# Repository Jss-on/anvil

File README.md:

# Anvil

**Hardware product development with explicit release gates and revision-bound evidence.**
Version **0.6.0** · Claude Code and Codex plugins · Proprietary license

Anvil carries a product from requirements and architecture through PCB fabrication, firmware,
mechanics, integration, EVT/DVT/PVT, market release, support and retirement. Its commands perform
authorized engineering work and keep missing external tests or approvals visible as blockers.

```mermaid
flowchart LR
  G0["G0 Opportunity"] --> G1["G1 Requirements"] --> G2["G2 Architecture"]
  G2 --> G3["G3 Prototype release"] --> G4["G4 EVT"] --> G5["G5 DVT"]
  G5 --> G6["G6 PVT"] --> G7["G7 Market release"] --> S["Support and retirement"]
  S -->|Controlled changes| G2
```

Electronics, firmware/services, mechanics, supply/manufacturing, quality/compliance and commercial
work proceed concurrently. The [lifecycle protocol](.claude/skills/anvil/references/lifecycle-protocol.md)
defines gates, owners, artifacts and checklists. The [research report](research/hardware-product-lifecycle.md)
and [original assessment](ASSESSMENT.md) explain the upgrade's basis.

## Use with Claude Code

Install the repository's marketplace in Claude Code, then its `anvil` plugin:

```text
/plugin marketplace add Jss-on/anvil
/plugin install anvil@anvil
```

For local development, load the actual packaged directory with `claude --plugin-dir ./claude-plugin`.
The repository's canonical command and skill files also support project-local development.
Do not assume editing this checkout changes an already cached installation; reload the local
plugin or update the installed package after publishing an authorized release.

| Command | Purpose |
|---|---|
| `/anvil` | Bounded custom metric loop or task routing |
| `/anvil:requirements` | Requirements, methods, owners, verification gates and applicability |
| `/anvil:build` | Concurrent product development, default target G3 |
| `/anvil:lifecycle` | Bring-up, EVT/DVT/PVT, market release and sustaining |
| `/anvil:improve` | Cost/area/mass/margin optimization with non-regression checks |
| `/anvil:evals` | Run analysis and evidence/gate review |

Examples:

```text
/anvil:build Goal: battery-powered environmental monitor Release: product Target: G3
/anvil:lifecycle Scope: ./sensor Target: G5 Action: execute
/anvil:improve Metric: bom_cost Scope: ./sensor Iterations: 10
```

## Use with Codex

Install and sign in using the [official Codex CLI setup](https://learn.chatgpt.com/docs/codex/cli).
Install Anvil's engineering tools under [Run the checks directly](#run-the-checks-directly).
From this checkout, register its local marketplace and install the native Codex plugin:

```sh
codex plugin marketplace add .
codex plugin add anvil@anvil
codex -C . --sandbox workspace-write
```

The [Codex marketplace](.agents/plugins/marketplace.json) selects the self-contained package
in [`plugins/anvil/`](plugins/anvil/.codex-plugin/plugin.json). Codex loads its `$anvil` skill;
Claude Code uses the separate marketplace and package above. This follows Codex's
[native plugin and marketplace format](https://learn.chatgpt.com/docs/enterprise/plugin-management).

Start a **new thread** after installation. In Codex CLI or the IDE extension, type `$` to select
Anvil, or paste a prompt such as:

```text
$anvil build Goal: battery-powered environmental monitor Scope: ./build-output/sensor Release: product Target: G3
$anvil lifecycle Scope: ./build-output/sensor Target: G5 Action: review
$anvil improve Metric: bom_cost Scope: ./build-output/sensor Iterations: 10
```

Send one prompt at a time. The skill also routes `requirements`, `evals`, and custom metric
loops. All six workflows use the same engineering protocols, Python checks, receipts and gates
as the Claude Code plugin. In the Codex app, select Anvil and describe the task in a new thread.

To work in an existing hardware repository, launch `codex -C <project-directory>` and use
`Scope: .`; installed Anvil tools resolve from the plugin cache. When working in this checkout,
`build-output/sensor` is ignored by Git; maintain the product's own source history and release
archive. Keep project outputs outside the plugin cache.

For a noninteractive review of an existing project, use single quotes so PowerShell and Bash
preserve the `$anvil` skill mention. See the [Codex CLI reference](https://learn.chatgpt.com/docs/developer-commands?surface=cli).

```sh
codex exec -C . --sandbox workspace-write 'Use $anvil lifecycle Scope: ./build-output/sensor Target: G3 Action: review. Report the actual gate result and blockers.'
```

For development without installation, open this checkout and ask Codex to read
`.claude/skills/anvil/SKILL.md` and the desired `.claude/commands/anvil/<workflow>.md` directly.
Use the checkout's `scripts/` and `templates/`. Installed plugins are cached copies; editing
this repository does not update an existing session.

Scope tailoring supports embedded/connected, robotics/industrial, medical and automotive
products; US, EU, Great Britain, Northern Ireland and Taiwan markets; Taiwan manufacture/export;
firmware, mechanics, radio, battery and cloud features. Classification and dates are reviewed
per product. Selecting a profile does not certify a design.

## Run the checks directly

Python 3.10+ standard library is the core dependency. Git tracks controlled source; KiCad CLI
is needed for ERC/DRC/exports and standalone ngspice for simulation. Use only the CAD, firmware,
HIL and authoring tools the project actually needs. On Windows, `scripts\doctor.cmd` locates
Git Bash; direct `uv run --no-project --offline python scripts/anvil.py ...` also works.

```sh
python scripts/anvil.py doctor --require-build
python scripts/anvil.py init ../sensor --scope product --sectors embedded,connected --markets US,EU --features electronics,firmware,mechanics,radio,battery
# Populate real requirements, artifacts and checks in the generated project.
python scripts/anvil.py plan ../sensor
python scripts/anvil.py manifest ../sensor
python scripts/anvil.py record ../sensor AUTO-ERC
python scripts/anvil.py record ../sensor AUTO-DRC
python scripts/anvil.py gate ../sensor G3
python scripts/anvil.py handoff ../sensor --write build --gate G3
```

Initialization creates incomplete templates and cannot produce a ready verdict by itself. For an
existing hardware project, copy/add the required files individually and preserve its existing work.
See the [CLI contract](.claude/skills/anvil/references/metrics.md) and
[evidence schema](.claude/skills/anvil/references/evidence-protocol.md) for command arrays,
receipts, strict table formats and exit statuses.

## Accuracy and outputs (0.6)

- **Rulebook.** About 12,000 cited rules (0.7; 6,900 in 0.6) extracted from the reference library, in the skill's
  `references/rulebook/`. Sources include IPC-2221C/6012F/A-610J, Brooks & Adam, Bogatin, Coombs & Holden,
  Hall/McCall, Hall & Heck, Archambeault, Williams, Paul, Pressman, Erickson, Pozar, Balanis, Bowick,
  Johnson & Graham (1993, 2003), Horowitz & Hill, Scherz & Monk, Ritchey, Mitzner, Wilson, Stringham, White
  and Cohen, each mined in full. Every rule carries its page, section, table or figure, and
  `bibliography.json` maps rule ids to IEEE references; each file's section 8 lists OCR losses and printed
  errata found while re-checking worked examples.
- **Cited calculations.** `design/rules.tsv` rows run textbook formulas as a gate check (`rules`). They cover
  trace temperature and current, IPC-2221 spacing, fusing, impedance, PDN target and decoupling, converter
  ripple and RHP zero, loop and common-mode radiation, slot shielding, I²C pull-ups, return loss, Friis
  link, patch antenna, thermal and mass.
- **Wired schematics.** `schematic sch/circuit.json pcb/board.kicad_sch` places KiCad symbols, draws real
  orthogonal wires and power symbols, then proves the drawing. KiCad must reload it, the fresh netlist
  must equal the spec, and ERC must be clean. `schematic-spec` converts an existing label-only drawing.
- **Evidence outputs.** `plots` renders ngspice corner waveforms and margin charts. `renders` produces
  schematic and PCB SVG/PDF/3D files. `fabpack` produces Gerber X2, drill, placement, IPC-2581,
  IPC-D-356 and STEP files, with every command logged and hashed.
- **Audit and paper.** `log` keeps iteration, decision and research ledgers for the modify→verify→keep
  loop. `report` writes `audit/AUDIT.md`, `audit.json` and an IEEEtran `paper.tex` with `refs.bib`. Both
  are built from the ledgers, receipts, BOMs and plots.

## Board truth (0.7)

Every board claim is now measured on the copper KiCad itself reports, read through KiCad's own Python with
zones refilled in memory. Nothing is taken from typed numbers.

- **Board, placement, routing.** `board` puts footprints and nets from the schematic onto a template board
  that carries the fabricator's stackup, outline and rules. `place` applies `design/placement.tsv`, and
  `route` runs Freerouting on a copy and checks the result with DRC.
- **Layout.** `layout` checks the routed copper against `design/nets.tsv` and `rf.tsv`:
  - IPC-2152 trace heating (Brooks & Adam fits) and via groups;
  - IPC-2221 spacing to every neighbour net;
  - field-solved Z0 and Zdiff with the real mask and coplanar gaps;
  - return-plane continuity and length matching;
  - RF via-fence pitch, pour stitching, matching-part distance and antenna keep-outs.
- **Signal integrity.** `si` turns each routed net into field-solved transmission lines, including via stubs,
  and simulates it in ngspice. It reports overshoot, ringback, delay and settling at every receiver.
- **Power integrity.** `pdn` computes impedance at the load. Each capacitor's mounted inductance is built from
  the copper: its fanout path, via pair and cavity spreading. Plane capacitance and the VRM are included, and
  the result is checked against Z_target.
- **Thermal.** `thermal` is a layered conduction model of the real copper and via barrels. It gives Tj for
  each part and a heat map.
- **EM.** `em` writes an openEMS FDTD model of the RF path: its nets and ground copper, ports where the
  connector pin or device lead enters each pad (driving the coplanar gaps over a launch cut-out), and the
  matching parts (capacitors as series ESR-ESL-C, inductors with the ESR of their Q). It
  saves Touchstone and plots; a `settled` row fails if the end of the run still moves a checked S-parameter.
  `sparams` applies the same limits to VNA measurements of the built board.
- **EMC estimate.** `emc` multiplies each net's loop area by the clock's trapezoid harmonics and compares the
  result with the FCC and CISPR limit lines.

**Validation.** Every solver is tested against an analytic anchor:

| Solver | Reference | Agreement |
|---|---|---|
| Z0, 2-D field solver | Cohn stripline, Hammerstad–Jensen microstrip | < 1 % |
| Thermal | K0 point source on a plate | < 0.1 % |
| SI | Lattice-diagram overshoot | exact |
| EMC harmonics | Paul's worked example | 0.05 dB |
| EM | 2-D solver on a 50 Ω microstrip | Zin within 1.1 %; ε_eff within 1.6 % (two-length, mean 1.1 %); line loss within 1.5 % of the analytic dielectric loss; \|S12 − S21\| < 3e-5 |
| EM, coplanar launch port | 2-D solver on a CPW over a 1.53 mm ground (an SMA pad over a cut-out) | Z0 from the S-matrix within 0.22 % over 1–3 GHz; S11 < −27 dB to 4 GHz; \|S12 − S21\| < 2e-3 |
| EM, antenna mode | Balanis patch design; cos² feed law | resonance within 3.2 % (mesh-converged to 0.15 %); feed law within 1 % |

**Still physical.** VNA measurement of RF paths, antenna pattern and efficiency, chamber EMC, and thermal
validation at EVT.

## Readiness means evidence

- All **75 research checklist items** are bundled, with **19 early applicability checkpoints**.
  Planning adds applicable automatic checks and every project requirement; deleting a required
  ledger row cannot improve readiness.
- `pass-rate` and `coverage` are diagnostics. `gate` requires exact due checks, matching methods,
  scoped artifacts, current file hashes and substantive review/external records.
- G3 distinguishes `PCB_FAB_READY`, `ASSEMBLY_READY` and `PRODUCT_BUILD_READY`. G5 is
  `DESIGN_QUALIFIED`, G6 `PRODUCTION_READY`, and G7 `MARKET_READY`. Earlier gates remain required.
- KiCad reports must come from successful fresh runs with valid schemas and active adjacent
  rule/project files. Simulation runs every declared corner and never falls back to old logs.
- BOM/cost/mass/budget and wiring inputs have strict numeric and source-join checks. Firmware
  and factory records identify builds, unit revisions, fixtures/calibration, attempts and rework.
- Changed design inputs invalidate G3+ evidence. Handoffs recompute the actual verdict and
  include blockers; stale or unsupported readiness is rejected before chaining.

Physical measurements, factory qualification and legal/customer approvals must come from actual
execution and responsible reviewers. Anvil verifies record structure and file integrity; it does
not authenticate approval identities, certify products, or replace a regulated quality system.
The filesystem receipt model assumes trusted editors; externally signed records/access controls
are needed where adversarial tampering or authenticated approvals are in scope.

No remote publication, supplier contact, purchase, hardware energization, firmware deployment,
filing or shipment happens without the session's authorization for that action. Local work and
reviewable packages proceed without repeated permission requests.

Optional failure triage is available with `Jev: shadow` in build/evals. The
[Jev triage guide](.claude/skills/anvil/references/jev-triage.md) describes the finding packet,
`TYPESAFE_API_KEY` or hidden `--prompt-key` input, and the standalone
`python -B scripts/jev_triage.py finding.json` command. It emits advisory JSON and never writes
designs or release evidence. The network client is separate from the hashed gate engine.
For a small live diagnostic replay, use
`python -B evals/jev/pilot.py cases.json new-run-directory --prompt-key`.

## Migrate from 0.4

1. Archive the old ledger as history. Add `anvil-project.json`, structured
   `hrs/requirements.tsv`, complete artifact roles and explicit check command arrays.
2. Run `plan`; migrate a prior observation only after its actual input/configuration, execution
   and review provenance is established. Old `evidence:path` strings are not receipts.
3. Put `<board>.kicad_dru` beside its matching PCB/project/schematic. A nested `pcb/rules/`
   deck is inactive. Only the reviewed JLCPCB two-layer starter is bundled.
4. Add `circuit` to simulation rows. Declare each swept parameter on its own `.param` line.
   `SKIP_NGSPICE` and implicit cached logs are rejected.
5. Replace subsystem-only ICD endpoints with physical pins, qualified ratings, voltage/protocol
   and mate pin lists. Product BOM `source` becomes `relative.csv#item_id`; budget sources use
   `relative.json#key` with explicit value and units. Record firmware/build and factory evidence.
6. Generate the release manifest, record/review checks, and run `gate`. Legacy `verdict <tsv>`
   stays `FAB_BLOCKED`. Renew affected receipts after configuration changes.

## Develop and verify

Canonical sources: `.claude/commands/`, `.claude/skills/anvil/`, `scripts/` and `templates/`.
`claude-plugin/` and `plugins/anvil/` are their byte-for-byte installable mirrors for Claude Code
and Codex. Edit canonical files, then sync. Each package has its own native manifest.

```sh
python -B tests/test_anvil.py
bash scripts/sync-plugin.sh
bash scripts/sync-plugin.sh --check
bash scripts/score-e2e-capability.sh
```

For local Codex updates, use `$plugin-creator` to refresh Anvil from this checkout's `anvil`
marketplace. Its update flow adds a version cachebuster and reinstalls the plugin; start a new
thread afterward. The base version stays aligned with `VERSION`.

Tests cover valid observations and the assessment's negative cases, cumulative lifecycle gates,
stale receipts/handoffs, sector/market tailoring, firmware/cost/factory records and both isolated
installed payloads, including workflow links. CI runs the Python contracts on Linux and Windows
and verifies both packages.
Optional native checks run with `ANVIL_NATIVE_TESTS=1` when KiCad/ngspice are installed.
`score-e2e-capability.sh` runs executable software checks; it no longer reports grep matches
as end-to-end physical product capability.

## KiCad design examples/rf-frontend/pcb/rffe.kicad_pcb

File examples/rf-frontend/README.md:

# rffe — Anvil showcase: 2.4 GHz gain block + 25 MHz reference clock

A complete Anvil project, taken from requirements to recorded G3 evidence. Every number below was produced by
Anvil's own commands on the KiCad files in this folder. Each one is quoted from a hashed receipt in `evidence/`;
none are typed in.

**Board:** 4 layers, 50 × 36 mm.
- **RF chain:** J1 → C1 → U2 (Mini-Circuits GALI-84+) → C2 → J2, on 50 Ω grounded-coplanar lines over the In1
  ground plane. The edge-launch SMA pads reference B.Cu through cut-outs in In1 and In2.
- **Bias tee:** 22 nH choke, 3 × 220 Ω 2512 from 12 V, 10 pF + 100 nF bypass.
- **Clock:** a 25 MHz oscillator drives a 33 Ω series-terminated SMA output.
- **Supply:** an AMS1117 makes +3V3 on an In2 plane.

> Showcase design. The GALI-84 and AMS1117 bias, θjb and output-impedance values are datasheet typicals
> marked "to confirm". This is not a product release.

## Reproduce

```sh
python tools/pipeline.py                         # schematic -> template -> board -> place + RF pre-routes -> Freerouting + DRC
python ../../scripts/anvil.py rules design       # cited sizing calculations
python ../../scripts/anvil.py layout  pcb/rffe.kicad_pcb design
python ../../scripts/anvil.py pdn     pcb/rffe.kicad_pcb design
python ../../scripts/anvil.py si      pcb/rffe.kicad_pcb design
python ../../scripts/anvil.py thermal pcb/rffe.kicad_pcb design
python ../../scripts/anvil.py emc     pcb/rffe.kicad_pcb design
python ../../scripts/anvil.py em      pcb/rffe.kicad_pcb design   # openEMS, ~50 min (4 port runs)
python ../../scripts/anvil.py fabpack pcb/rffe.kicad_pcb fab && python ../../scripts/anvil.py renders .
python tools/write_ledgers.py && python tools/declare_release.py
python ../../scripts/anvil.py plan . && python ../../scripts/anvil.py manifest . && python ../../scripts/anvil.py record . AUTO-...
python ../../scripts/anvil.py gate . G3 && python ../../scripts/anvil.py report .
```

`tools/` holds the project-specific steps an engineer or agent would script:
- `size_rf_line.py`: field-solver width/gap table.
- `make_template.py`: stackup, outline, planes and the SMA launch cut-outs.
- `make_routes.py`: RF lines, clock line, fence, launch/thermal/stitching vias and plane fanouts, all computed from
  the placed pads.
- `place_schematic.py`: functional sheet layout.
- `declare_release.py`, `write_ledgers.py`.

## What the loop found and fixed (`audit/iterations.tsv`)

| # | Found by | Problem | Fix |
|---|---|---|---|
| 1 | `schematic` | Netlist mismatch on the first run only | Generator nondeterminism (set order); fixed in Anvil, regression test added |
| 2 | `drc` | 137 → 20 violations: edge-launch pads, zone islands, silkscreen | SMA pull-back, scoped edge rule, island removal, placement |
| 3 | `drc` | Floating +3V3 plane, fragmented ground pour | Plane fanouts and stitching pre-routed |
| 4 | `layout` | RF fence gaps and pour tips beyond λ/10 and λ/20 at 5 GHz | Greedy fence, launch vias, gap-fill stitching: 58/58 |
| 5 | `rules` | Bias resistors at 51.6 % of rating at 13.2 V (2× derating, WILSON-394) | 2 × 150 Ω → 3 × 220 Ω: 35 % |
| 6 | `thermal` | GALI-84 at 130.3 °C against a 130 °C limit after the extra resistor | R1 moved, 2 × 3 thermal vias: 129.0 °C |
| 7 | `si` | ngspice stalled on sub-ps line fragments | Fixed in Anvil: fragments below the time step are merged |
| 8 | `em` | openEMS field energy never decayed (a −11 dB plateau), so no S-parameters | Fixed in Anvil (below) |
| 9 | `em` | SMA centre pad (1.5 mm) over In1 at 0.2 mm is an 18 Ω section: `rf_in` S11 −6.8 dB, S21 −1.26 dB | In1/In2 cut-out under the J1/J2 centre pads (JOHNSON03-1307): the pad references B.Cu, 47.8 Ω; S11 −15.9 dB |
| 10 | `rules` + `em` | 100 pF DC blocks are 8.8 Ω *inductive* at 2.5 GHz: far above their self-resonance | 10 pF C0G, series-resonant near the band: 3.1 Ω (BOGATIN-2128, ARCH-067) |
| 11 | `em` | S11 then read −14.95 dB with Zin 42 + j14 Ω: the inductive 100 pF had been masking the launch *port's* own inductance, a 1.5 mm tall sheet down to B.Cu | Fixed in Anvil: over a cut-out the port drives the coplanar gaps (validated against the 2-D solver); S11 −17.1 dB |

Iteration 8 was diagnosed with 16 point field probes and truncated-record comparisons, not the energy log. The
port signals had decayed 50 dB while the "energy" stayed flat. Removing the ideal 100 pF lumped capacitor let the
model converge: spread over the mesh, an ideal C rings losslessly. The EM engine now:
- models capacitors as series ESR-ESL-C;
- models only the analysed and ground nets;
- places each port where the pin or lead enters its pad;
- runs to −50 dB;
- reports a `settled` row, so an unconverged result cannot pass.

The first converged run then exposed iteration 9, a real layout flaw that every earlier check had passed.
Iteration 11 is the loop checking its own instrument: a model artifact, found because the numbers moved the
wrong way after a change that should have helped, then fixed and validated before the result was trusted.

## Results

Receipts bind release `da83c6a3…` (`release-manifest.json`, 33 controlled files) and the checker code.

| Check | Result | Tightest margin |
|---|---|---|
| AUTO-ERC / AUTO-DRC | 0 / 0 violations | KiCad 10.0.5 on the release files |
| AUTO-CONNECTIVITY | 5/5 | netlist equals `sch/circuit.json` |
| AUTO-SIM | 2/2 | bias-node ripple −15.1 dB at 100 kHz (worst corner) against −3 dB |
| AUTO-RULES | 11/11 | DC block 3.06 Ω against 5 Ω; bias current 103.6 mA in 100 ± 10 mA |
| AUTO-LAYOUT | 58/58 | RF Z0 50.0 Ω; fence ≤ λ/10 and stitching ≤ λ/20 at 5 GHz |
| AUTO-PDN | 1/1 | +3V3 Zmax 0.80 Ω against 1.65 Ω |
| AUTO-SI | 4/4 | CLK_OUT ringback 9.8 % against 20 %; settled in 0.55 ns against 5 ns |
| AUTO-THERMAL | 5/5 | U2 junction 129.0 °C against 130 °C (thin: confirm at EVT) |
| AUTO-EMC | 2/2 | CLK_OUT 32 dB under CISPR 32 Class B, 26 dB after the 6 dB design margin |
| AUTO-EM | not yet recorded | `rf_in` probe passes: S11 −17.1 dB (limit −15), S21 −0.21 dB (limit −0.6). `rf_out` diverges in openEMS 0.37 (below) |

**Open issue: `rf_out`.** With the bias tee in the model, every run diverges after the pulse: the energy decays to
about −20 dB, then grows without bound from roughly 30k timesteps. Bisection so far:
- Any single series-type lumped part triggers it, the choke alone or the capacitors alone, even though each is
  stable in a small test model.
- Collapsing the parts to single-edge lines does not help, and neither does cutting the bias feed at the region
  edge.

The all-resistor control run had not finished when this snapshot was taken. Anvil rejects a diverged run
(NaN energy or non-finite port signals) instead of reporting it, so AUTO-EM stays open until `rf_out` converges.

Figures: `analysis/em/*.png` (S-parameters against the limits), `analysis/layout/copper-*.png`,
`analysis/thermal/thermal.png`, `analysis/pdn/pdn-_3V3.png`, `analysis/si/si-CLK_OUT.png`,
`analysis/emc/emc-cispr32_b.png`, `audit/plots/P-1.png` (bias ripple at the tolerance corners).

## Gate

`anvil.py gate . G3` returns `G3_BLOCKED`: AUTO-EM (above) and the 41 human sign-offs:
- 2 G0 opportunity reviews;
- 15 G1 requirement and compliance-plan reviews;
- 6 G2 architecture reviews;
- 8 G3 release reviews;
- 10 requirement closures (REQ-HR-001 … 010).

Anvil will not record an approval it would have to invent. A reviewer closes each one in three steps:
1. `anvil.py prepare . <check> <evidence files>`
2. Fill in reviewer, role, decision and record.
3. `anvil.py record . <check> --evidence evidence/<check>.draft.json`

## Audit documentation

- `audit/AUDIT.md` and `audit/audit.json`: requirements, 11 research sources, 9 decisions, 12 iterations, every
  receipt with its transcript and margins, the BOM, figures, the release manifest and IEEE references.
- `audit/paper/paper.tex` + `refs.bib`: IEEE conference skeleton with the requirement, decision, execution, margin
  and iteration tables and every verification figure. The prose sections are for the author.
- `fab/`: gerbers, drill, placement, IPC-2581, IPC-D-356 test netlist, STEP; `audit/renders/`: schematic PDF/SVG,
  board SVG/PNG.

## What stays physical

- VNA S-parameters of the built board (HR-011 at G4). The EM model has no SMA body, solder mask or conductor loss,
  and its lumped launch port stands 1.5 mm tall.
- The gain block's own S-parameters, from the vendor file, not from copper.
- Chamber EMC: the emission figure is an estimate (±10 dB).
- A thermocouple or IR check of U2: the thermal margin is under 1 °C in the model.

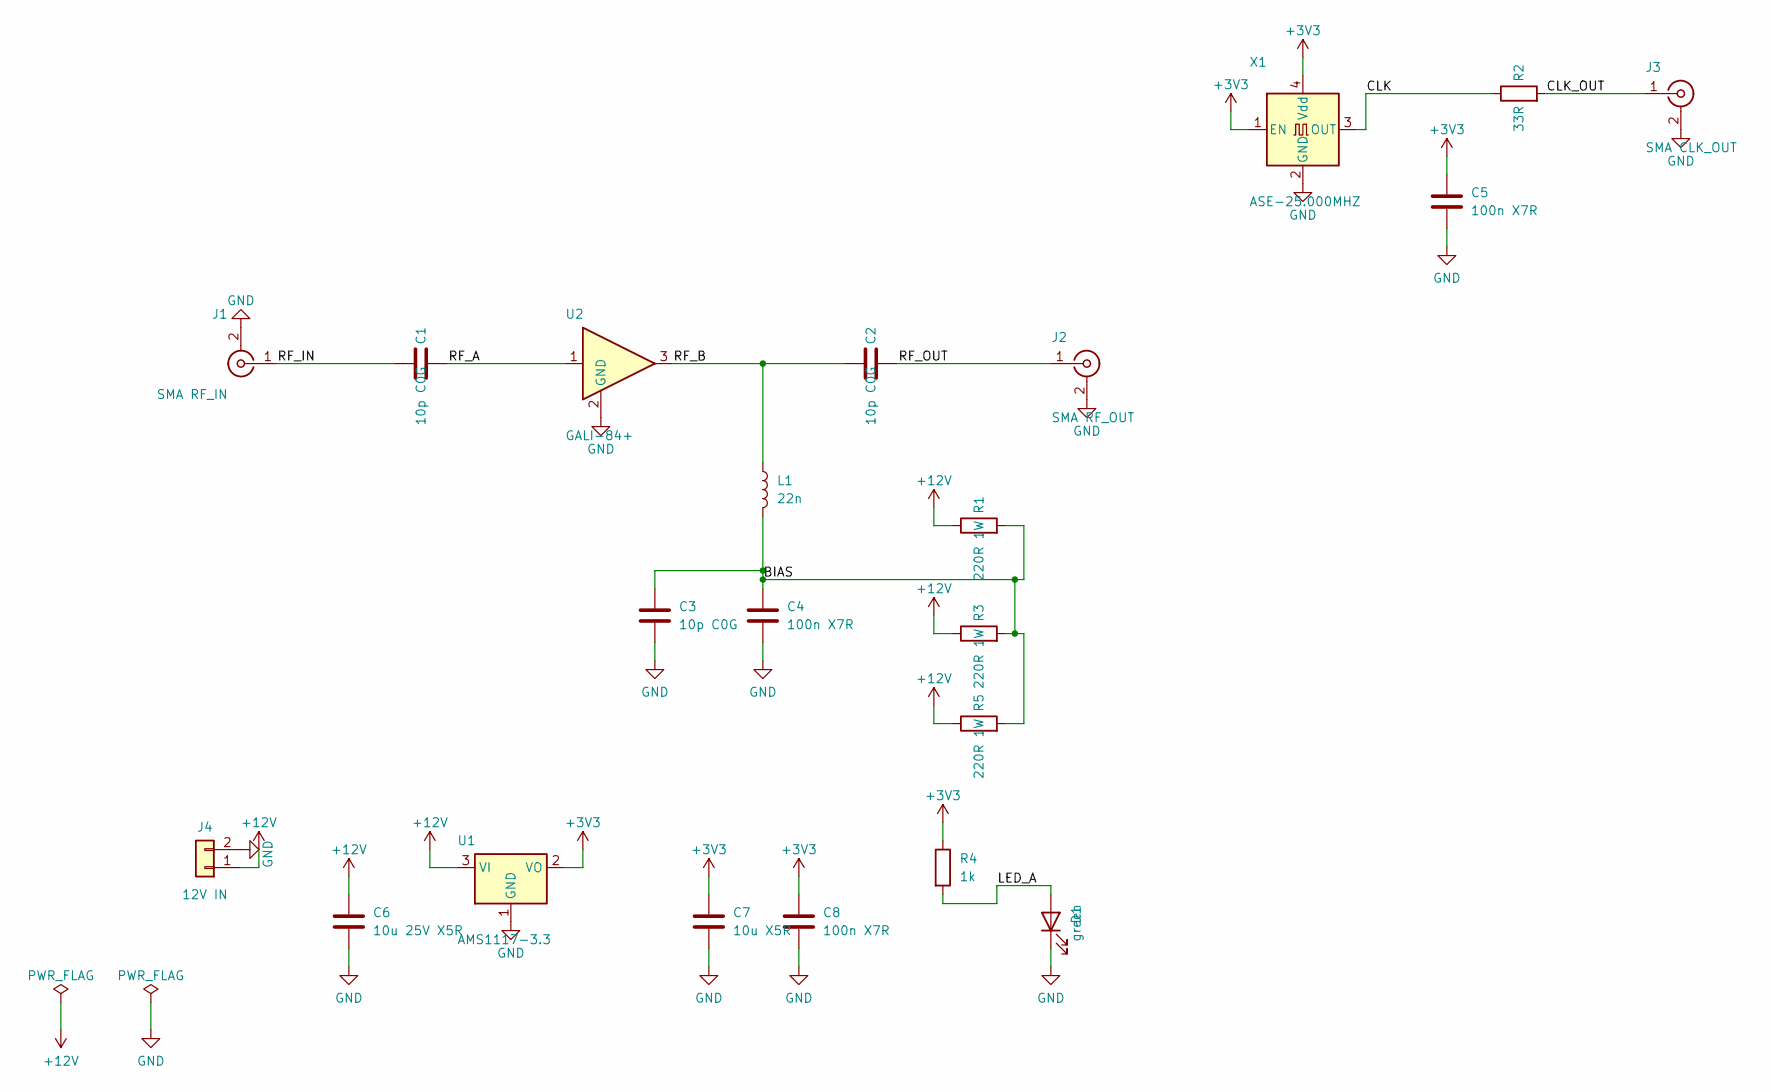
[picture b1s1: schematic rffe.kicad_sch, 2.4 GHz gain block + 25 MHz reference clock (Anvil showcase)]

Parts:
C1, C2, C3: 10p C0G; C_0402_1005Metric
C4, C5, C8: 100n X7R; C_0402_1005Metric
C6: 10u 25V X5R; C_0805_2012Metric
C7: 10u X5R; C_0805_2012Metric
D1: green; LED_0603_1608Metric
J1: SMA RF_IN; SMA_Amphenol_132289_EdgeMount
J2: SMA RF_OUT; SMA_Amphenol_132289_EdgeMount
J3: SMA CLK_OUT; SMA_Amphenol_132289_EdgeMount
J4: 12V IN; JST_PH_B2B-PH-K_1x02_P2.00mm_Vertical
L1: 22n; L_0603_1608Metric
R1, R3, R5: 220R 1W; R_2512_6332Metric
R2: 33R; R_0402_1005Metric
R4: 1k; R_0402_1005Metric
U1: AMS1117-3.3; SOT-223-3_TabPin2
U2: GALI-84+; SOT-89-3
X1: ASE-25.000MHZ; Oscillator_SMD_Abracon_ASE-4Pin_3.2x2.5mm

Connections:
+3V3: C5.1, C7.1, C8.1, R4.1, U1.2 (VO), X1.1 (EN), X1.4 (Vdd)
+12V: C6.1, J4.1, R1.1, R3.1, R5.1, U1.3 (VI)
/BIAS: C3.1, C4.1, L1.2, R1.2, R3.2, R5.2
/CLK: R2.1, X1.3 (OUT)
/CLK_OUT: J3.1 (In), R2.2
/LED_A: D1.2 (A), R4.2
/RF_A: C1.2, U2.1
/RF_B: C2.1, L1.1, U2.3
/RF_IN: C1.1, J1.1 (In)
/RF_OUT: C2.2, J2.1 (In)
GND: C3.2, C4.2, C5.2, C6.2, C7.2, C8.2, D1.1 (K), J1.2 (Ext), J2.2 (Ext), J3.2 (Ext), J4.2, U1.1 (GND), U2.2 (GND), X1.2 (GND)

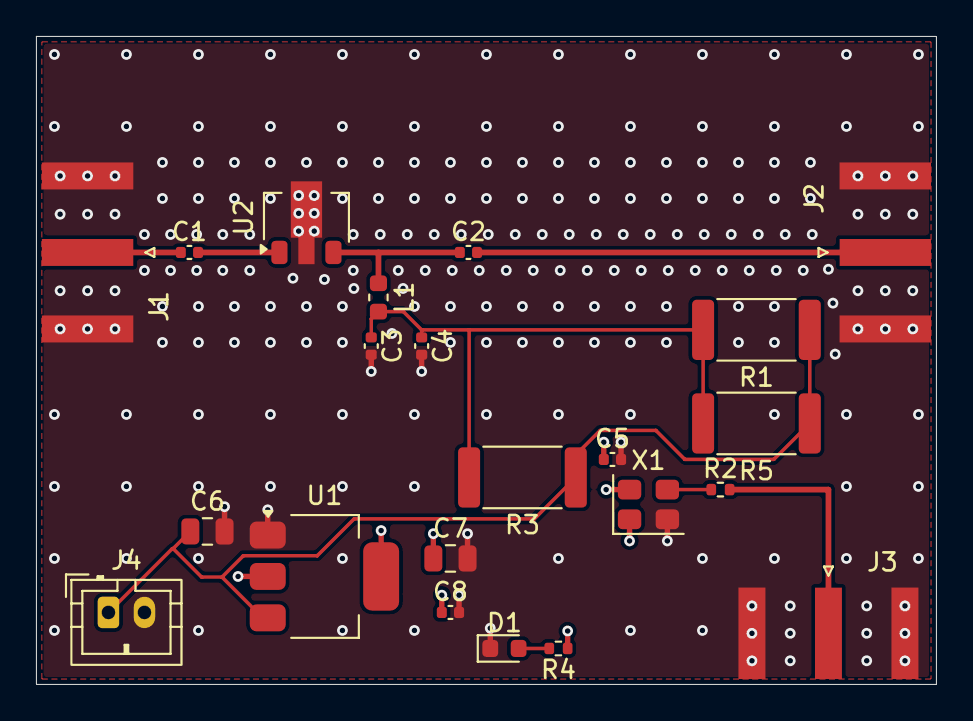
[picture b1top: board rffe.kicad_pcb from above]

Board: 4 copper layers, 50.0 x 36.0 mm, 22 parts (0 on the bottom side), 11 nets.
